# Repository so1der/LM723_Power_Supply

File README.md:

# LM723 Power Supply

So this is a linear power supply based on the LM723 IC. It utilizes the LM723 chip and a TIP35C transistor for voltage regulation. The TIP35 transistor generates significant heat, so it requires effective cooling — specifically a heatsink and ideally a fan, though a large heatsink alone may suffice.

Resistor RV1 is used to adjust the output voltage.

The current limiter engages when the output current exceeds by approximately 3A.

An N11BW enclosure was used for the power supply - custom front and rear panels were designed for it, and the corresponding stl files are available in the repository.

---

Перед вами - лінійний блок живлення на мікросхемі LM723. Він використовує мікросхему LM723 та транзистор TIP35C для стабілізації напруги. Транзистор TIP35 буде доволі сильно грітись, тому він потребує гарне охолодження - радіатор, та в ідеалі вентилятор, але можна обійтись і просто великим радіатором.

Резистор RV1 використовується для підлаштування вихідної напруги.

Після приблизно 3А струму на виході - спрацьовує обмежувач струму.

В якості корпусу для блоку живлення був використаний корпус N11BW, для якого були спроєктовані передня та задня панелі - їх stl файли також знаходяться в репозиторії.

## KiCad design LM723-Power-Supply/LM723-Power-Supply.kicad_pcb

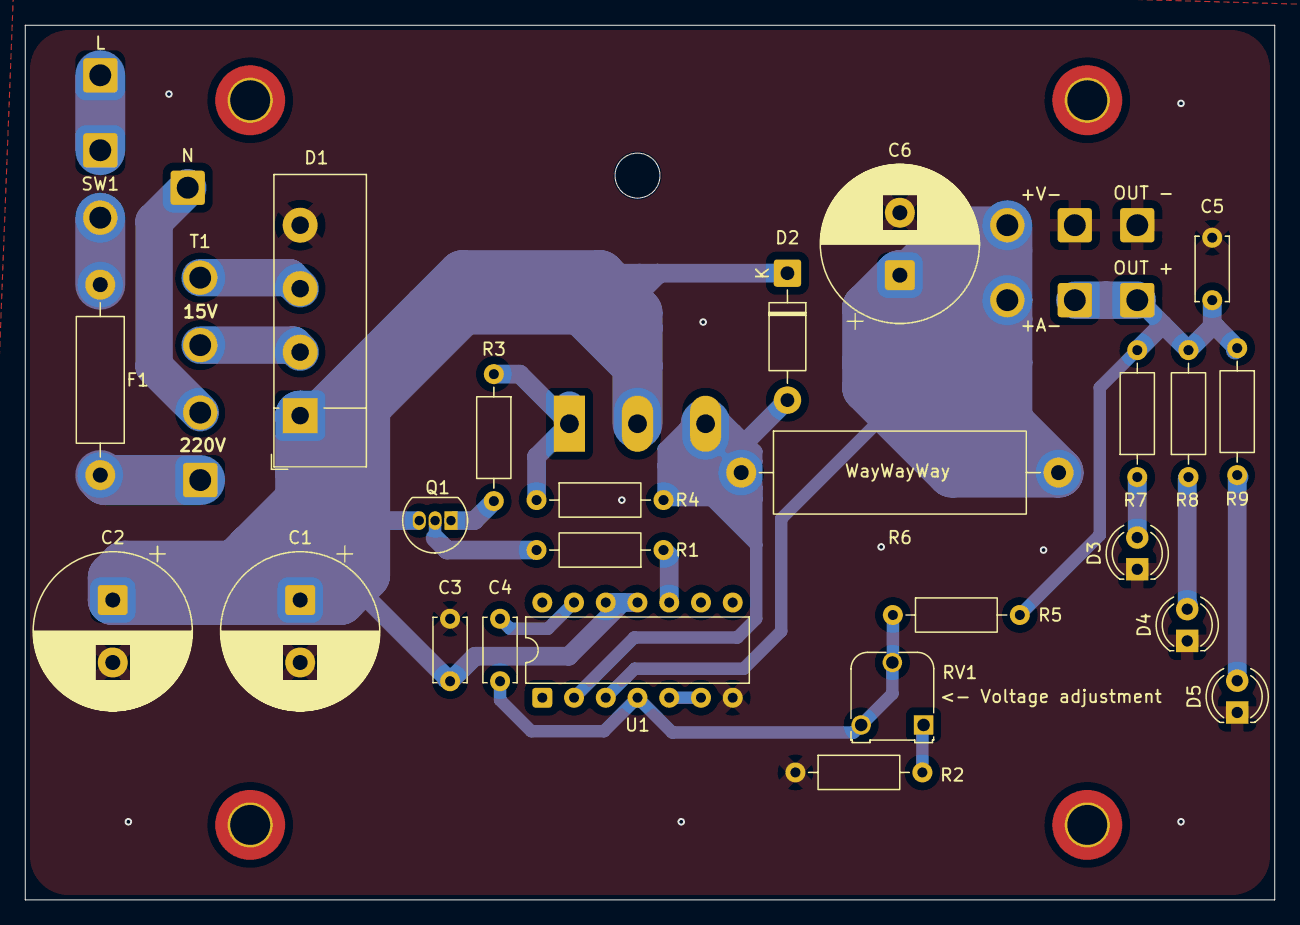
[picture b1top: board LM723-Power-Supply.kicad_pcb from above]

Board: 2 copper layers, 100.0 x 70.0 mm, 33 parts (1 on the bottom side), 22 nets.

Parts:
+A-: Ammeter_DC; SolderWire-1sqmm_1x02_P5.4mm_D1.4mm_OD2.7mm
+V-: Voltmeter_DC; SolderWire-1sqmm_1x02_P5.4mm_D1.4mm_OD2.7mm
C1, C2: 2200uF 25V; CP_Radial_D12.5mm_P5.00mm
C3, C5: 100 nF; C_Disc_D5.0mm_W2.5mm_P5.00mm
C4: 500 pF; C_Disc_D5.0mm_W2.5mm_P5.00mm
C6: 1000uF 25V; CP_Radial_D12.5mm_P5.00mm
D1: KBU610; Diode_Bridge_Vishay_KBU
D2: 1N4007; D_DO-41_SOD81_P10.16mm_Horizontal
D3, D4, D5: LED; LED_D4.0mm
F1: 500 mA; R_Axial_DIN0411_L9.9mm_D3.6mm_P15.24mm_Horizontal
L: LINE; SolderWire-1sqmm_1x01_D1.4mm_OD2.7mm
N: NEUT; SolderWire-1sqmm_1x01_D1.4mm_OD2.7mm
OUT +: OUT +; SolderWire-1sqmm_1x01_D1.4mm_OD2.7mm
OUT -: OUT -; SolderWire-1sqmm_1x01_D1.4mm_OD2.7mm
Q1: 2N2222; TO-92_Inline
Q2: TIP35C; TO-247-3_Horizontal_TabUp
R1, R4: 470R; R_Axial_DIN0207_L6.3mm_D2.5mm_P10.16mm_Horizontal
R2, R5, R7, R8, R9: 1K; R_Axial_DIN0207_L6.3mm_D2.5mm_P10.16mm_Horizontal
R3: 47R; R_Axial_DIN0207_L6.3mm_D2.5mm_P10.16mm_Horizontal
R6: 0.22R, 3W; R_Axial_Power_L20.0mm_W6.4mm_P25.40mm
RV1: 200R; Potentiometer_Runtron_RM-065_Vertical
SW1: SW_DPST_x2; SolderWire-1sqmm_1x02_P5.4mm_D1.4mm_OD2.7mm
T1: 220-15VAC; SolderWire-1sqmm_1x04_P5.4mm_D1.4mm_OD2.7mm
U1: LM723; DIP-14_W7.62mm

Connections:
GND: +V-.1 (-), C1.2, C2.2, C3.2, C5.2, C6.2, D1.4 (-), D3.1 (K), D4.1 (K), D5.1 (K), OUT -.1 (Pin_1_1), R2.1, U1.7 (V-)
unnamed: C1.1, C2.1, C3.1, D1.1 (+), D2.1 (K), Q1.3 (C), Q2.2 (C), U1.11 (VC), U1.12 (V+)
unnamed: D2.2 (A), Q2.3 (E), R4.2, R6.1, U1.2 (ILIM)
unnamed: D3.2 (A), R7.1
unnamed: D4.2 (A), R8.1
unnamed: D5.2 (A), R9.2
unnamed: L.1 (Pin_1_1), SW1.1 (A)
unnamed: N.1 (Pin_1_1), T1.2 (AB)
unnamed: +A-.2 (+), +V-.2 (+), C6.1, R6.2, U1.3 (CSEN)
unnamed: Q1.2 (B), R1.2
unnamed: Q1.1 (E), R3.2
unnamed: Q2.1 (B), R3.1, R4.1
unnamed: R2.2, RV1.1
unnamed: F1.1, SW1.2 (B)
unnamed: F1.2, T1.1 (AA)
unnamed: D1.2, T1.3 (SA)
unnamed: D1.3, T1.4 (SB)
unnamed: U1.5 (+), U1.6 (VREF)
unnamed: C4.1, R5.1, RV1.2, RV1.3, U1.4 (-)
unnamed: C4.2, U1.13 (FC)
unnamed: R1.1, U1.10 (Vout)
V_OUT: +A-.1 (-), C5.1, OUT +.1 (Pin_1_1), R5.2, R7.2, R8.2, R9.1
